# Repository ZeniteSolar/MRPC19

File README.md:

# MRPC19
Módulo Raspberry PI CAN

As conexões com o MCP2515 foram realizadas com o SPI0 do Raspberry Pi:

| RASPBERRY PI |  Description |
|-------------:|--------------|
|       GPIO08 | MCP2515 SS   |
|       GPIO09 | SPI0 MOSI    |
|       GPIO10 | SPI0 MOSI    |
|       GPIO11 | SPI0 SCK     |
|       GPIO25 | MCP2515 INT  |

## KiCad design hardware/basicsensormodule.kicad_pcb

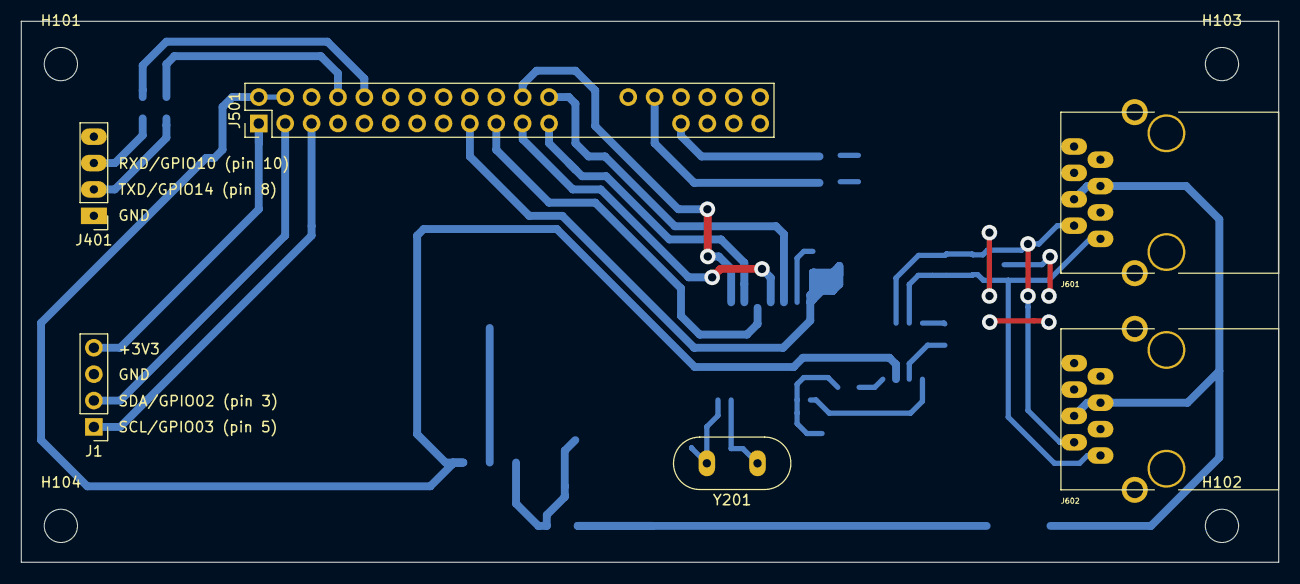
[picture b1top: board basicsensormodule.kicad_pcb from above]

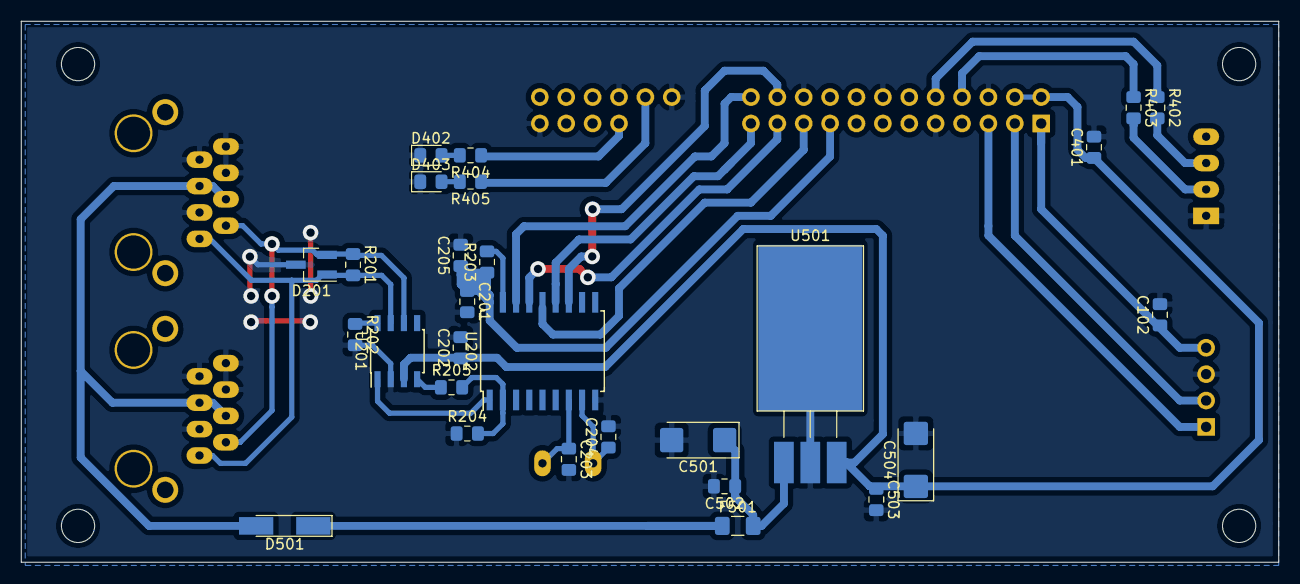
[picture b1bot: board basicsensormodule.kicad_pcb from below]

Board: 2 copper layers, 121.0 x 52.1 mm, 38 parts (28 on the bottom side), 30 nets.

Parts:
C102, C201, C202, C205, C401, C502, C503: 100nF; C_0805_2012Metric_Pad1.15x1.40mm_HandSolder
C203, C204: 22pF; C_0805_2012Metric_Pad1.15x1.40mm_HandSolder
C501, C504: 1uF; CP_EIA-6032-20_AVX-F_Pad2.25x2.35mm_HandSolder
D201: pesd1can; SOT-23_Handsoldering
D402, D403: LED_RED; LED_0805_2012Metric_Pad1.15x1.40mm_HandSolder
D501: LL4148; D_MiniMELF_Handsoldering
F501: 500mA; Fuse_1206_3216Metric_Pad1.42x1.75mm_HandSolder
H101, H102, H103, H104: MountingHole; MountingHole_3.2mm_M3
J1: I2C; PinHeader_1x04_P2.54mm_Vertical
J401: USART; PinHeader_1x04_P2.54mm_Vertical
J501: Raspberry_Pi_2_3; PinHeader_2x20_P2.54mm_Vertical
J601, J602: RJ45; RJ45_YH59_01
R201: 120; R_0805_2012Metric_Pad1.15x1.40mm_HandSolder
R202: 4k7; R_0805_2012Metric_Pad1.15x1.40mm_HandSolder
R203: 10k; R_0805_2012Metric_Pad1.15x1.40mm_HandSolder
R204: 22K; R_0805_2012Metric_Pad1.15x1.40mm_HandSolder
R205: 10K; R_0805_2012Metric_Pad1.15x1.40mm_HandSolder
R402, R403, R404, R405: 1k; R_0805_2012Metric_Pad1.15x1.40mm_HandSolder
U201: MCP2551-I/SN; SOIC-8_3.9x4.9mm_P1.27mm
U202: MCP2515-xSO; SOIC-18W_7.5x11.6mm_P1.27mm
U501: LM7805; TO-220-3_Horizontal_TabDown_SMD
Y201: 16MHz; Crystal_HC49-U_Vertical

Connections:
+5V: C202.1, C401.1, C503.1, C504.1, J501.2, J501.4, U201.3, U501.3
/CANBUS CONN/CAN_H: D201.1, J601.1, J602.1, R201.2, U201.7
/CANBUS CONN/CAN_L: D201.2, J601.2, J602.2, R201.1, U201.6
/CANBUS/3V3: C102.1, C201.1, C205.1, J1.4, J501.1, J501.17, R203.1, U202.18
/CANBUS/CS: J501.24, U202.16
/CANBUS/INT: J501.22, U202.12
/CANBUS/RXCAN: R204.2, R205.2, U202.2
/CANBUS/TXCAN: U201.1, U202.1
/MCU/LED1: J501.32, R405.1
/MCU/LED2: J501.33, R404.1
/MCU/SCL: J1.1, J501.5
/MCU/SDA: J1.2, J501.3
/MCU/USART_RX: J501.10, R402.1
/MCU/USART_TX: J501.8, R403.1
/MISO: J501.21, U202.15
/MOSI: J501.19, U202.14
/POWER SUPPLY/+18V_IN: D501.2, J601.4, J601.5, J602.4, J602.5
/POWER SUPPLY/+18V_OUT: C501.1, C502.1, F501.2, U501.1
/SCK: J501.23, U202.13
GND: C102.2, C201.2, C202.2, C203.2, C204.2, C205.2, C401.2, C501.2, C502.2, C503.2, C504.2, D201.3, D402.1, D403.1, J1.3, J401.1, J501.6, J501.9, J501.14, J501.20, J501.25, J501.30, J501.34, J501.39, J601.3, J601.6, J601.7, J601.8, J602.3, J602.6, J602.7, J602.8, R202.2, R204.1, U201.2, U202.9, U501.2
unnamed: C203.1, U202.7, Y201.1
unnamed: C204.1, U202.8, Y201.2
unnamed: D402.2, R404.2
unnamed: D403.2, R405.2
unnamed: D501.1, F501.1
unnamed: J401.2, R403.2
unnamed: J401.3, R402.2
unnamed: R202.1, U201.8
unnamed: R203.2, U202.17
unnamed: R205.1, U201.4

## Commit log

2019-05-07 Arquivos originais do MVC19 adicionados
2019-05-08 Subsubstituição do atmega pelo raspberry
    No esquemático.
2019-05-08 Adicão da alimentação de uma folha para outra .
    Alimentação de 3V3.
2019-05-09 PCB atualizada com as mudanças do raspberry
    Foram adicionadas as mudanças do conector do raspberry e retirado algumas coisas não necessárias.
2019-05-09 Adicinado o conector raspberry na pbc
    Adicionado o conector raspbeery na pbc e feito ajustes.
2019-08-01 Project cleaned
2020-01-19 3D exported
